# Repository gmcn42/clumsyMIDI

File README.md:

# clumsyMIDI
A Raspberry Pi expansion board containing a MIDI interface, DAC, and OLED display requiring only through-hole soldering skills. This is primarily intended as an all-in-one hardware solution for the [mt32-pi Roland MT-32 emulator](https://github.com/dwhinham/mt32-pi) but all features are usable with Raspberry Pi OS, too.

## Table of contents

<!-- toc -->
- [Features](#features)
- [Schematic and BOM](#schematic-and-bom)
- [How to get the PCB](#how-to-get-the-pcb)
  * [PCB Specs](#pcb-specs)
- [Assembly](#assembly)
  * [An ⚠IMPORTANT⚠ note on the DAC board solder bridges](#an-important-note-on-the-dac-board-solder-bridges)
  * [Rewiring MIDI Thru to Out](#rewiring-midi-thru-to-out)
  * [Mechanical Parts](#mechanical-parts)
  * [A General Note](#a-general-note)
- [Software Config](#software-config)
  * [mt32-pi](#mt32-pi)
  * [Raspberry Pi OS](#raspberry-pi-os)

<!-- tocstop -->

## Features
* TI PCM5102 I2S HiFi DAC (using the ubiquitous GY-PCM5102 carrier board)
* GPIO MIDI interface with in, out, and thru
* 0.91" OLED display
* large-ish 5V bypass capacitor which may help with slightly weak power supplies
* works with [mt32-pi](https://github.com/dwhinham/mt32-pi) and Raspberry Pi OS
* no SMT soldering required, so it should be suitable for clumsy DIYers like me ;)

## Schematic and BOM
Schematic and BOM are available in the [`pdf/` subfolder](https://github.com/gmcn42/clumsyMIDI/tree/main/pdf).

## How to get the PCB
You can get a zip file with the Gerber files from the [releases page](https://github.com/gmcn42/clumsyMIDI/releases/) and let your favorite board house build the PCB. Alternatively, you can also order directly from PCBWAY via [this link](https://www.pcbway.com/project/shareproject/clumsyMIDI___Raspberry_Pi_expansion_board.html) for convenience. Full disclosure: If you use the link, PCBWAY will donate 10% of the PCB price to me. I want to make clear that the PCB design is completely free and you are in no way obligated or even encouraged to use that link.

In case you want to make changes to the PCB before ordering somewhere, you can use [KiCAD](https://kicad.org/) and import the project.

***⚠IMPORTANT NOTE:⚠*** Before soldering down the DAC board please make *sure* you check the [assembly instructions below about the DAC's solder bridges](#an-important-note-on-the-dac-board-solder-bridges). Their factory configuration appears to be varying from supplier to supplier and you may need to change them.

### PCB Specs
* PCB size (height * width): 56mm * 65mm
* Layers: 2
* Minimum drill size: 0.6mm
* Minimum track size: 0.25mm (=9.84mil)
* Minimum track clearance/spacing: 0.25mm (=9.84mil)
* Surface finish: by preference (the pictured boards are lead-free HASL but pretty much anything will do)

## Assembly
As all components are through-hole, you should get by with basic soldering skills. It is usually the best idea to start with the flattest components and work your way up. The 40-Pin GPIO socket should be soldered on last, also remember that it goes on the *bottom* :).

As shown in the BOM, I recommend socketing U1 and U2 as they are the most likely casualties if defective MIDI devices are connected for some reason. Be mindful of the ICs' orientation. The notch of the 74HCT14 should be where the notch is on the silkscreen. Likewise, the H11L1's dot (marking for Pin 1) should also face the in the direction of the notch on the silkscreen. If inserted correctly, U1 and U2 will "face outward and away from each other".

It is possible to leave out some components, e.g. if you only need MIDI-In. Consult [the schematic](https://github.com/gmcn42/clumsyMIDI/blob/main/pdf/clumsyMIDI-schematic.pdf) for details.

As I happily noticed people are actually really starting to build these things, I have opened the [discussions page](https://github.com/gmcn42/clumsyMIDI/discussions) of this project. If you have questions about anything related to the board and its assembly, feel free to open a topic!

### An ⚠IMPORTANT⚠ note on the DAC board solder bridges
Before soldering on the DAC board please double-check that the solder bridges on the bottom of your GY-PCM5102 are configured as in the following picture:

So: 1, 2, and 4 to L and 3 to H. This should be the standard factory-set config but at least one builder encountered a board with an unconnected bridge resulting in the DAC being permanently muted. If you have a multimeter you might also want to check good connection from the board's pins to rule out bad solder joints. FLT, FMT, and DEMP should have almost 0Ω to GND while XSMT should have almost 0Ω to pin 20 (top right) of the DAC chip itself.

If yours are un- or wrongly set, you'll have to resolder them.

### Rewiring MIDI Thru to Out
In standard configuration, the MIDI Thru output is available on a 5-pin header due to space constraints. If you do not need MIDI Out but want a MIDI Thru, it is possible to route the Thru signal to the MIDI-Out socket instead of the pin header. In that case, leave J4, R1, and R5 unpopulated and solder a wire between the footprint pads of J4 and R1 marked with a circle on the silkscreen, as shown in these two pictures (click for larger version):

### Mechanical Parts
Be sure to use some kind of standoffs or similar when connecting clumsyMIDI to the PI. Without them, the board may sit lopsided and come in contact with the HDMI port, potentially causing a short circuit. Apart from that, it's more mechanically stable and simply looks nicer :). The BOM contains the brass standoffs I am using in the pictures.

### A General Note
Use caution and common sense while working with electronics, especially while soldering stuff. As stated in the license, I am offering this PCB design as-is incuding any and all defects it may have and will not be held liable for any harm that comes to you or others as a result of using/building/looking at it.

## Software Config
### mt32-pi
Follow the setup instructions on their site and then set the following options in `mt32-pi.cfg`:
```
usb = off
output_device = i2s
type = ssd1306_i2c
```
The option `gpio_thru` will also work with the MIDI Out port on clumsyMIDI, so use at your preference.

### Raspberry Pi OS
You need to add the following to `/boot/config.txt` to get GPIO MIDI, I2S DAC, and I2C support
```
enable_uart=1
dtoverlay=pi3-miniuart-bt
dtoverlay=midi-uart0

dtparam=i2s=on
dtoverlay=hifiberry-dac

dtparam=i2c_arm=on,i2c_arm_baudrate=400000
```
Also you need to comment out or remove the line `dtparam=audio=on`

Additionally for I2C support, add the following line to `/etc/modules`:
```
i2c-dev
```

To get regular ALSA MIDI support you need to bridge `/dev/ttyAMA0` and an ALSA MIDI port. You can do this with [`ttymidi`](https://github.com/cjbarnes18/ttymidi).
Once you have it compiled and installed, run the following in a terminal:
```
sudo ttymidi -s /dev/ttyAMA0 -b 38400
```
If you are asking yourself why it needs to be set to 38400 Baud: The line `dtoverlay=midi-uart0` causes the Pi's UART base clock to be slightly lowered, so that 38400 (a common RS232 baud rate) effectively becomes 31250 Baud which is MIDI-compatible.

Now you when run `aconnect -l` in another terminal, you should see a new MIDI client. Something similar to:
```
client 128: 'ttymidi' [type=user,pid=920]
    0 'MIDI out     '
    1 'MIDI in      '
```
Somewhat confusingly, the out/in naming is reversed because it is from the perspective of `ttymidi`. That means 'MIDI in' is what it receives from another application and then forwards to the UART. So if you want to play something on a synth connected to the clumsyMIDI's output, the correct command will be
```
aplaymidi -p 128:1 somefile.mid
```

The I2C display is supported by the [Adafruit SSD1306 Python library](https://github.com/adafruit/Adafruit_Python_SSD1306.git), among others.

Have fun!

clumsyMIDI ©2020 by Andreas Zdziarstek.<br>This work is licensed under a [Creative Commons Attribution-ShareAlike 4.0 International License](https://creativecommons.org/licenses/by-sa/4.0/).<br>

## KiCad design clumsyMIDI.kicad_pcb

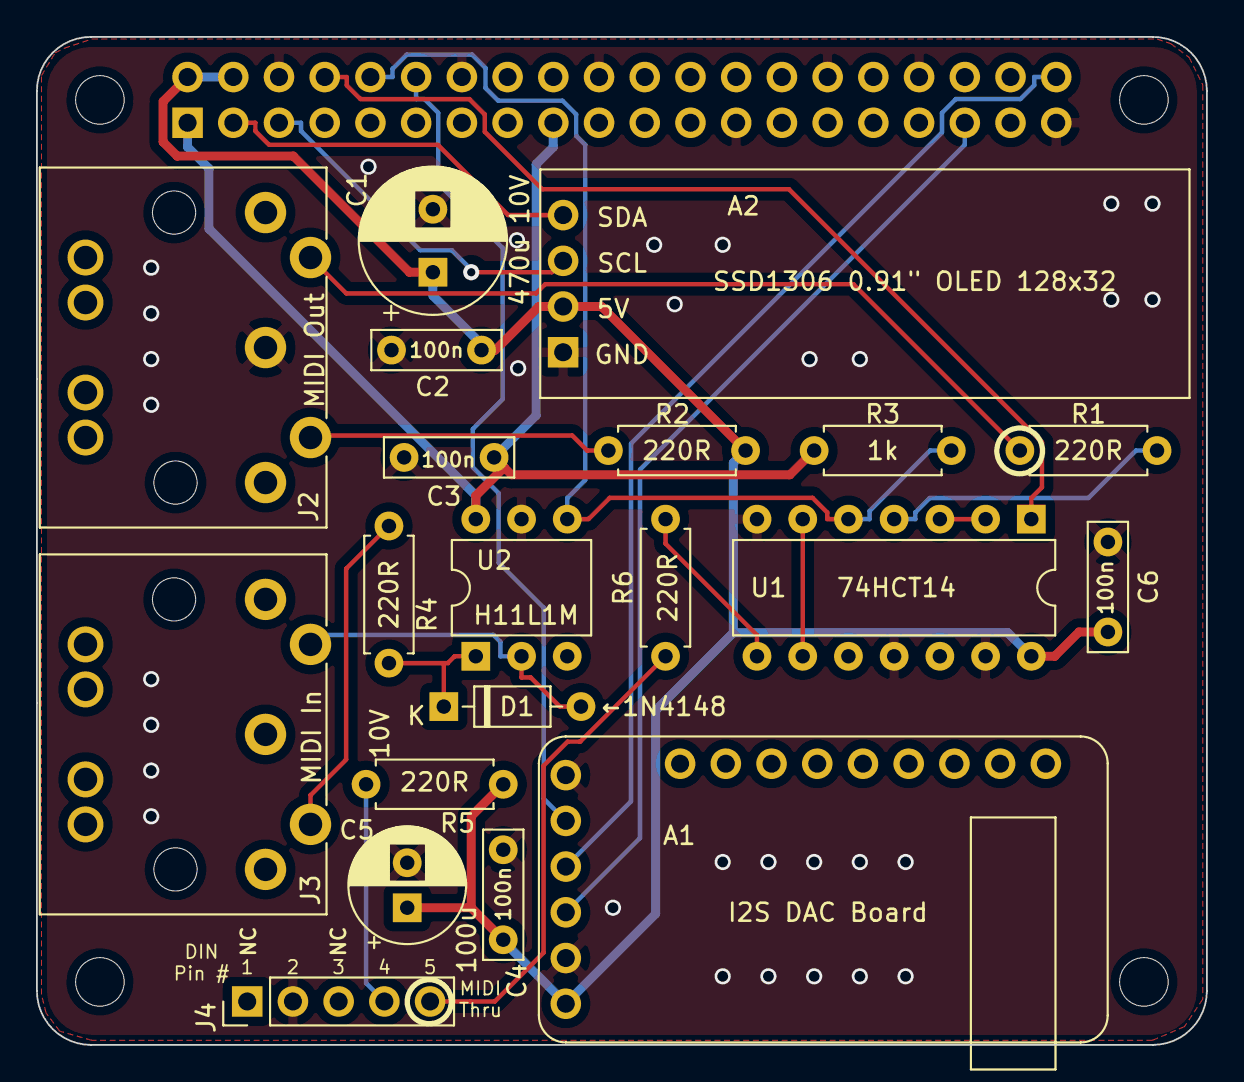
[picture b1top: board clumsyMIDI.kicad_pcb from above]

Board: 2 copper layers, 65.0 x 56.0 mm, 25 parts (1 on the bottom side), 21 nets.

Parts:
A1: GY-PCM5102
A2: SSD1306 Header; SSD1306_128_32
C1: 470u 10V; CP_Radial_D8.0mm_P3.50mm
C2, C3, C4, C6: 100n; C_Rect_L7.0mm_W2.0mm_P5.00mm
C5: 100u; CP_Radial_D6.3mm_P2.50mm
D1: 1N4148; D_DO-35_SOD27_P7.62mm_Horizontal
J2: MIDI Out Jack; MultiDIN5
J3: MIDI In Jack; MultiDIN5
J4: MIDI Thru Jack; PinHeader_1x05_P2.54mm_Vertical
MK1, MK2, MK3, MK4: M2.5; MountingHole_2.7mm_M2.5
P1: Conn_02x20_Odd_Even; PinSocket_2x20_P2.54mm_Vertical
R1, R2, R4, R5, R6: 220R; R_Axial_DIN0207_L6.3mm_D2.5mm_P7.62mm_Horizontal
R3: 1k; R_Axial_DIN0207_L6.3mm_D2.5mm_P7.62mm_Horizontal
U1: 74HCT14; DIP-14_W7.62mm
U2: H11L1M; DIP-6_W7.62mm

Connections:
+3V3: C3.1, P1.1, P1.17, R3.1, U2.6
+5V: A1.6, A2.2, C1.1, C2.2, C4.1, C5.1, C6.2, P1.2, P1.4, R2.1, R5.1, U1.14
/GPIO15(RXD0): P1.10, R3.2, U1.5, U2.4
GND: A1.1, A1.5, A2.1, C1.2, C2.1, C3.2, C4.2, C5.2, C6.1, J2.2, J4.2, P1.6, P1.9, P1.14, P1.20, P1.25, P1.30, P1.34, P1.39, U1.7, U1.11, U1.13, U2.5
I2C_SCL: A2.3, P1.5
I2C_SDA: A2.4, P1.3
I2S_BCLK: A1.2, P1.12
I2S_DATA: A1.3, P1.40
I2S_LRCLK: A1.4, P1.35
unnamed: D1.1, R4.2, U2.1
unnamed: D1.2, J3.5, U2.2
unnamed: J2.4, R2.2
unnamed: J2.5, R1.1
unnamed: J3.4, R4.1
unnamed: J4.4, R5.2
unnamed: J4.5, R6.1
unnamed: R1.2, U1.4
unnamed: R6.2, U1.8
unnamed: U1.2, U1.3
unnamed: U1.6, U1.9
TX_TTL: P1.8, U1.1

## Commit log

2020-11-26 init
2020-11-26 Added PDF BOM and schematic
2020-11-26 Add mechanical parts to BOM
2020-11-26 BOM formatting.
2020-11-26 Create LICENSE
    CC BY SA 4.0
2020-11-26 Update README.md
    fix PCBWAY link
2020-11-26 Add some pictures
2020-11-29 Picture resizing with small/large versions. Illustration of Thru/Out rewiring.
2020-11-29 Add PCB specs for board houses to README
2020-12-02 fixed the MIDI connector symbols in the schematic (no PCB change)
2020-12-07 Clarify MIDI/ttymidi setup on Raspberry Pi OS
    Clarify MIDI/ttymidi setup on Raspberry Pi OS, also added the i2c-dev kernel module thing for the display which I forgot before
2020-12-18 Add picture of solder bridges on DAC board.
2020-12-18 Add instructions about DAC solder bridges
2020-12-18 Grammar and missing sentence
2020-12-19 Make DAC board note more visible
2020-12-19 Add TOC
2020-12-19 Fix TOC
2020-12-19 Add toc link

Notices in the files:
clumsyMIDI.kicad_pcb:
PCB © 2020 by Andreas Zdziarstek, released under CC BY-SA 4.0 license
see https://creativecommons.org/licenses/by-sa/4.0
